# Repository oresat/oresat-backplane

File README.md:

# OreSat Backplane

## Background

The [OreSat](http://oresat.org) CubeSat bus uses a card cage / backplane system based on a 1 Mbps Controller Area Network (CAN) bus and a 2 cell Lithium ion battery power bus (6.0 - 8.4 V). There are ~ 8 cards per CubeSat "U", and the board is meant to be general purpose enough to allow for some card swapping. The RF lines, however, are microstrips on the backplane PCB so the backplane must be rev'd for changes in the RF cards. There are three sets of connectors:

1. 40 pin "Main" connector, which has !shutdown, CAN1, power, CAN2, OreSat power Domain (OPD) lines, and then 5 shared spare pins for custom card interconnects.
2. SMPM RF conncectors, which allows up to 3 RF connector per card and allows for 50 ohm microstrips to be run up and down the the board.
3. 20 pin "Auxiliary" connectors, used on the all but the "end" cards (top and bottom cards), which are for future inter-card communication. Good for Ethernet, for example.

The backplane now comes in two flavors: a 1U backplane, and a 2U backplane.

## Mechanical Specifications

All mechanical specifications for this board are from the SolidWorks model which is in the 'oresat-structure' repo, specifically see the 'Backplane' folder. Some notes on the mechanical design:

- Ring of bare copper on the back is for thermal contact. Assumes annodized Aluminum, so no electrical contact on this ring.
- Backplane is grounded to the Aluminum frame on the internal four fasteners; this requires preparing the Aluminum for an electrical connection.
- Square cutouts on the top and bottom are for the solar connectors to reach the end cards. Note that on the 1U backplane, the bottom cutout is not used.
- Weird cutouts above and below square solar connector cutouts are for shoulder bolts (3 mm Shoulder Diameter, 2 mm Shoulder Length, M2 x 0.4 mm Thread, McMaster Carr #[90263A111](https://www.mcmaster.com/90263a111)) that precisely locates the PCB while allowing some flexing due to differences in thermal expansion between the Aluminum frame and the PCB.
- All other fasteners are M2 x 0.4 x 4 mm.

## Electrical Specifications

The board is designed for a [4 layer stackup](https://docs.oshpark.com/services/four-layer/) from [OSH Park](https://oshpark.com/) which has better RF performance than regular 2 layer board runs.

The connectors that we use on this puppy are the:

- **1.27 mm through-hole vertical socket connectors:**
    - 40 pin main connector
       - Samtec SFM-120-01-S-D-LC
       - 3D CAD: https://www.samtec.com/partnumber/sfm-120-01-s-d-lc
       - Drawing: http://suddendocs.samtec.com/prints/sfm-1xx-xx-xxx-d-xxx-mkt.pdf
       - Brochure: http://suddendocs.samtec.com/catalog_english/sfm.pdf
       - SFM footprint: http://suddendocs.samtec.com/prints/sfm-thd.pdf
    - 20 pin auxiliary connector
       - Samtec SFM-110-01-S-D-LC
       - 3D CAD: https://www.samtec.com/partnumber/sfm-110-01-s-d-lc
       - Drawing: http://suddendocs.samtec.com/prints/sfm-1xx-xx-xxx-d-xxx-mkt.pdf
       - Brochure: http://suddendocs.samtec.com/catalog_english/sfm.pdf
       - SFM footprint: http://suddendocs.samtec.com/prints/sfm-thd.pdf

- **RF (70 cm, L band, S band)**
   - Molex 073300-011X
   - SMPM Connector Plug, Male Pin 50 Ohm Surface Mount, Through Hole Solder, $13.84/ea @ 10
   - Molex (w/CAD): https://www.molex.com/molex/products/datasheet.jsp?part=active/0733000110_RF_COAX_CONNECTORS.xml&channel=Products&Lang=en-US
   - We've done a detailed characteraziation of OSH Park's 4 layer process, and found that 0.38 mm is the correct width for a 50 ohm microstrip.

- **CAN termination**
   - We'll use split termination, using two 60 ohm resistors with a center tapped capacitor for reduced EMI.
   - Resistors
      - 60.4 +/- 1% ohms. Might consider higher if the number of notes (~ 20) adds too much parallel resistance)
      - Usually there's only 2V (differential) across the 120 ohm termination resistors = 16 mA = 33 mW of power dissipation.
      - In the event of a bus short, there's 8.4 V across 120 ohms is 70 mA = 590 mW of power dissipation. That's ~ 300 mW across each of the 60 ohm resistors. Yikes.
      - ISO 11898-2 also requires 220 mW for the termination resistors, for whatever that's worth.
      - There exist 0.5 W 1206 resistors (?!) so although that's for an air rating, we'll still choose it, since larger than 1206 resistors are a tight fit
   - Capacitor
      - ISO 11898-2 doesn't seem to say anything about the capacitance, and the internets tend to say weird things. Unclear on this value.
      - TI's [Controller Area Network Physical Layer Requirements](http://www.ti.com/lit/an/slla270/slla270.pdf) suggests 4.7 nF to make the f_3dB = 1.1 MHz.
      - Seems awfully close to our 1 Mbps bus, so let's bump that down to 1 nF which is f_3db = 5.3 MHz.

- **Debug connector**
   - Harwin M55-6001642R (same family as the solar and end cap connectors)
   - Located on the back side of the backplane, it's a 16 pin 1.27 mm connector that gives external access to CAN busses, VBUS, and the UART lines. It sits in the 1U solar module "cutout".
   - For the external connector board, see the `backplane-debug` folder in the `oresat-flatsat` repo.

## Versions

- 1U
   - v1.0 - First fabbed 1U, but never assembled. For old frames (v1.1 frames), no -Z end cap connector, no debug connector.
   - v1.1 - Added -Z end cap connector. Fabbed roughly 2020-09-01, two assembled.
   - v1.2 - Added 1.27 mm debug connector, which tended to short. Fabbed 2020-12-08. Originally delivered on OreSat0.0 but never flown.
   - v2.0 -new backplane "v2" signal pinout (less power, more signals, UART lines, CAN bus bridging) and new non-shorting debug connector. Made new debug port board and breakout. Also corrected RF ports, including L1 band microstrip and S band strip to -Z end cap. Fabbed 2021-11-01 and installed on OreSat0.1 handed off to Spaceflight, ready for launch!
- 2U
   - v1.0 - First backplane. 2 layer board, RF connector array, aux and main connectors. Fabbed 2018/10/02.
   - v1.1 - End Cards now use 40 pin connector, solar connectors now actually fit. Fabbed 2019/02/25.
   - V2.0 - Switched to 4 layer board, removed RF connector array, used actual microstrips tuned to the 4 layer OSH Park process. Fabbed 2019/07/01.
   - v2.1 - Updated to latest backplane DXF, reducing all sides by 0.15 mm. Fixed solar connector cutout areas that were lopsided. Added CAN termination resistors. Moved RF connectors to latest (2020/02/15) locations. NOT YET FABBED.
   - vHASP - Made for the NASA HASP mission, fabbed, but never used.
   - V2.2 - Updated to FrameV2 and Oresat0.5 card locations

## LICENSE

Copyright the Portland State Aerospace Society, 2022.

This source describes Open Hardware that is licensed under CERN-OHL-S v2, or any later version.

You may redistribute and modify this source and make products using it under the terms of the CERN-OHL-S v2 (https://ohwr.org/cern_ohl_s_v2.txt).

This source is distributed WITHOUT ANY EXPRESS OR IMPLIED WARRANTY, INCLUDING OF MERCHANTABILITY, SATISFACTORY QUALITY AND FITNESS FOR A PARTICULAR PURPOSE. Please see the CERN-OHL-S v2 for applicable conditions.

Source location: https://github.com/oresat/

As per CERN-OHL-S v2 section 4, should You produce hardware based on this source, You must where practicable maintain the Source Location visible on the external case of the Gizmo or other products you make using this source.

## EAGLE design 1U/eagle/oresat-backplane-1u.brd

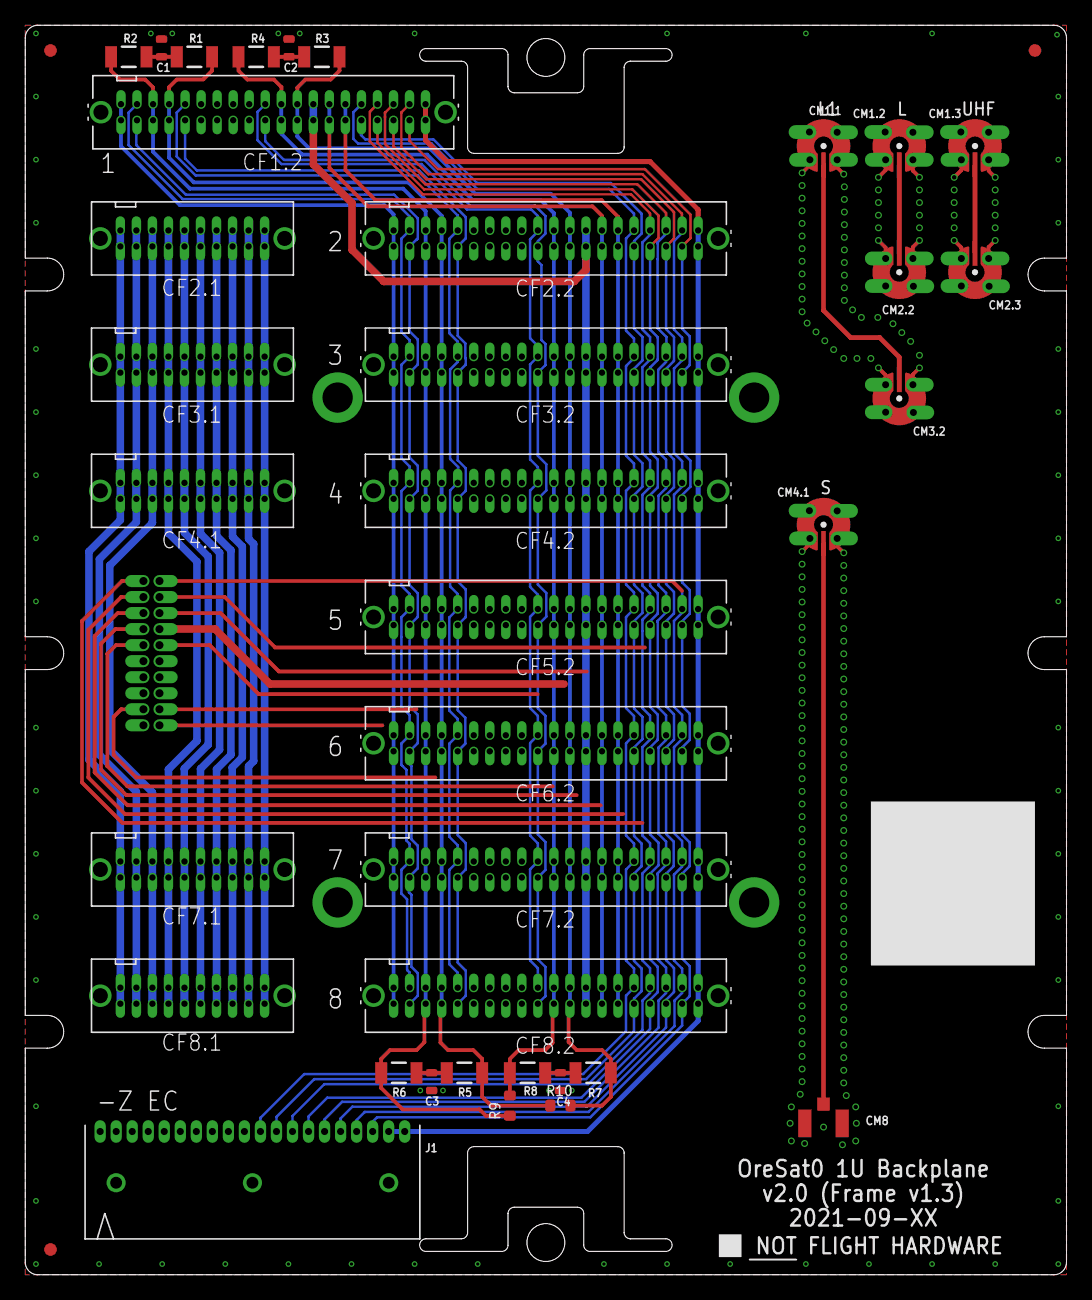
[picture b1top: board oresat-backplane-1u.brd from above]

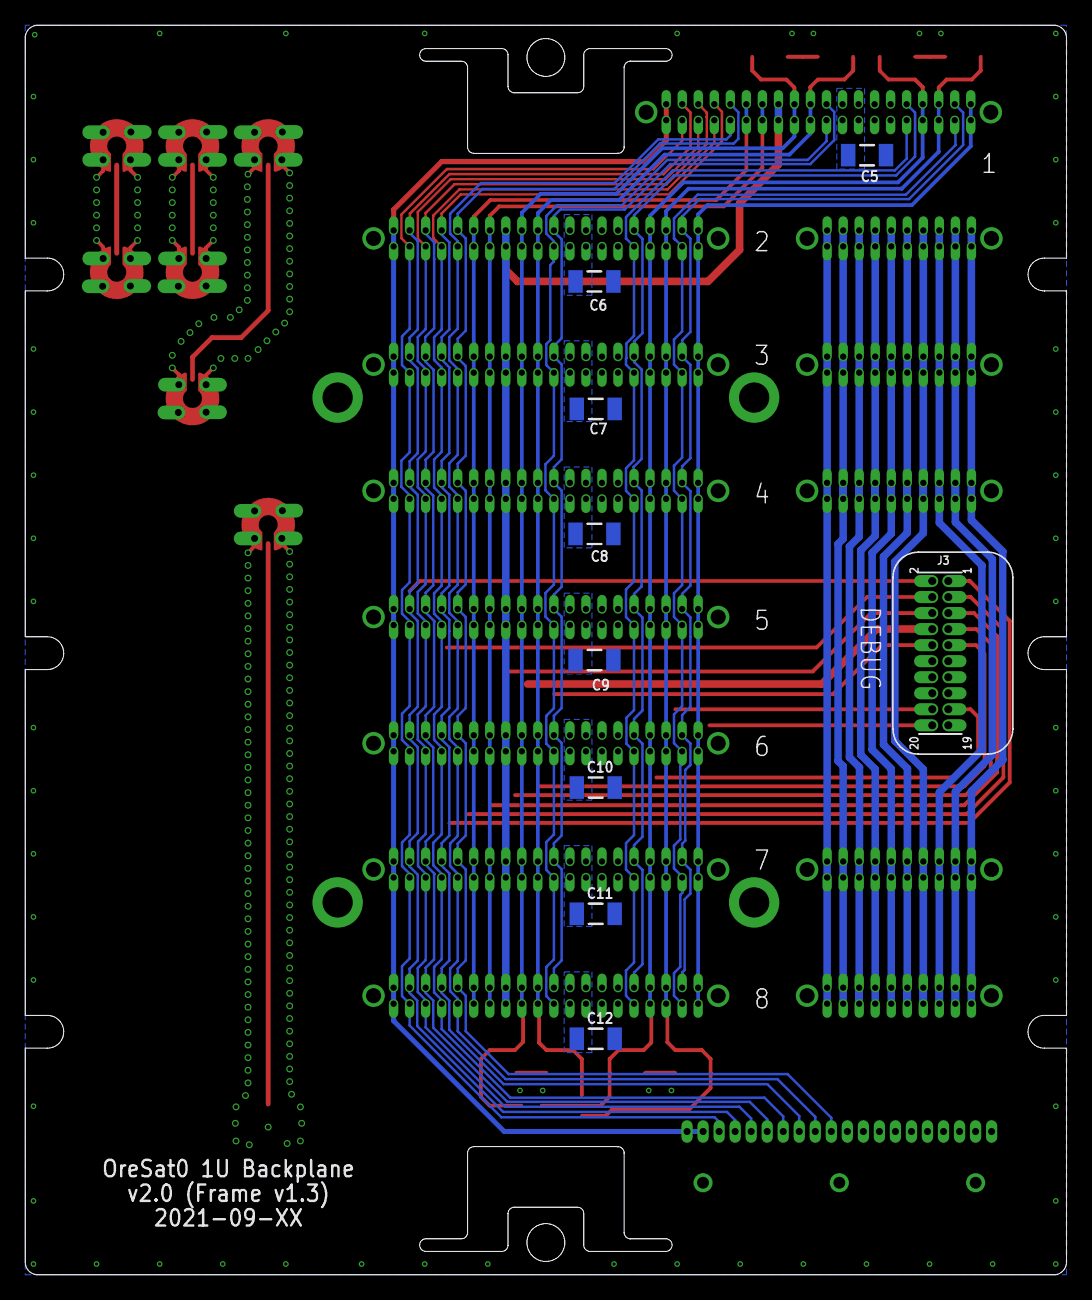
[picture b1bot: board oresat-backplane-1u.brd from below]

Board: 4 copper layers, 82.5 x 99.0 mm, 49 parts (9 on the bottom side), 43 nets.

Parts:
C1, C2, C3, C4: 1n; .0603-C-NOSILK
C5, C6, C7, C8, C9, C10, C11, C12: 1206-B
CF1.2, CF2.2, CF3.2, CF4.2, CF5.2, CF6.2, CF7.2, CF8.2: SFM-120-X1-XXX-D
CF2.1, CF3.1, CF4.1, CF7.1, CF8.1: SFM-110-X1-XXX-D-LC
CM1.1, CM1.2, CM1.3, CM2.2, CM2.3, CM3.2, CM4.1: J-MOLEX-SMPM-73300-0111X
CM8: U.FL-R-SMA; U.FL-R-SMT
FIDUCIAL1, FIDUCIAL2, FIDUCIAL3: FIDUCIAL-1.0X2.0
J1: 5-104196-5
J3: HARWIN-M50-3501042
R1, R2, R3, R4, R5, R6, R7, R8: 60.4; 1206-C
R9, R10: .0603-B-NOSILK
U$1: FLIGHMARKERNEW; FLIGHTMARKER_NEW_BOARDS

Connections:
!SD: CF1.2.39, CF1.2.40, CF2.2.39, CF2.2.40, CF3.2.39, CF3.2.40, CF4.2.39, CF4.2.40, CF5.2.39, CF5.2.40, CF6.2.39, CF6.2.40, CF7.2.39, CF7.2.40, CF8.2.39, CF8.2.40, J3.20
AUX-1: CF2.1.1, CF2.1.2, CF3.1.1, CF3.1.2, CF4.1.1, CF4.1.2, CF7.1.1, CF7.1.2, CF8.1.1, CF8.1.2
AUX-2: CF2.1.3, CF2.1.4, CF3.1.3, CF3.1.4, CF4.1.3, CF4.1.4, CF7.1.3, CF7.1.4, CF8.1.3, CF8.1.4
AUX-3: CF2.1.5, CF2.1.6, CF3.1.5, CF3.1.6, CF4.1.5, CF4.1.6, CF7.1.5, CF7.1.6, CF8.1.5, CF8.1.6
AUX-4: CF2.1.7, CF2.1.8, CF3.1.7, CF3.1.8, CF4.1.7, CF4.1.8, CF7.1.7, CF7.1.8, CF8.1.7, CF8.1.8
AUX-5: CF2.1.9, CF2.1.10, CF3.1.9, CF3.1.10, CF4.1.9, CF4.1.10, CF7.1.9, CF7.1.10, CF8.1.9, CF8.1.10
AUX-6: CF2.1.11, CF2.1.12, CF3.1.11, CF3.1.12, CF4.1.11, CF4.1.12, CF7.1.11, CF7.1.12, CF8.1.11, CF8.1.12
AUX-7: CF2.1.13, CF2.1.14, CF3.1.13, CF3.1.14, CF4.1.13, CF4.1.14, CF7.1.13, CF7.1.14, CF8.1.13, CF8.1.14
AUX-8: CF2.1.15, CF2.1.16, CF3.1.15, CF3.1.16, CF4.1.15, CF4.1.16, CF7.1.15, CF7.1.16, CF8.1.15, CF8.1.16
AUX-9: CF2.1.17, CF2.1.18, CF3.1.17, CF3.1.18, CF4.1.17, CF4.1.18, CF7.1.17, CF7.1.18, CF8.1.17, CF8.1.18
AUX-10: CF2.1.19, CF2.1.20, CF3.1.19, CF3.1.20, CF4.1.19, CF4.1.20, CF7.1.19, CF7.1.20, CF8.1.19, CF8.1.20
CAN1_H: CF1.2.33, CF1.2.34, CF2.2.33, CF2.2.34, CF3.2.33, CF3.2.34, CF4.2.33, CF4.2.34, CF5.2.33, CF5.2.34, CF6.2.33, CF6.2.34, CF7.2.33, CF7.2.34, CF8.2.33, CF8.2.34, J3.17, R1.1, R5.1, R10.1
CAN1_L: CF1.2.35, CF1.2.36, CF2.2.35, CF2.2.36, CF3.2.35, CF3.2.36, CF4.2.35, CF4.2.36, CF5.2.35, CF5.2.36, CF6.2.35, CF6.2.36, CF7.2.35, CF7.2.36, CF8.2.35, CF8.2.36, J3.18, R2.1, R6.1, R9.1
CAN2_H: CF1.2.17, CF1.2.18, CF2.2.17, CF2.2.18, CF3.2.17, CF3.2.18, CF4.2.17, CF4.2.18, CF5.2.17, CF5.2.18, CF6.2.17, CF6.2.18, CF7.2.17, CF7.2.18, CF8.2.17, CF8.2.18, J3.9, R3.1, R7.1, R10.2
CAN2_L: CF1.2.19, CF1.2.20, CF2.2.19, CF2.2.20, CF3.2.19, CF3.2.20, CF4.2.19, CF4.2.20, CF5.2.19, CF5.2.20, CF6.2.19, CF6.2.20, CF7.2.19, CF7.2.20, CF8.2.19, CF8.2.20, J3.10, R4.1, R8.1, R9.2
GND: C1.2, C2.2, C3.2, C4.2, C5.2, C6.2, C7.2, C8.2, C9.2, C10.2, C11.2, C12.2, CF1.2.27, CF1.2.28, CF1.2.29, CF1.2.30, CF1.2.LC1, CF1.2.LC2, CF2.1.LC1, CF2.1.LC2, CF2.2.27, CF2.2.28, CF2.2.29, CF2.2.30, CF2.2.LC1, CF2.2.LC2, CF3.1.LC1, CF3.1.LC2, CF3.2.27, CF3.2.28, CF3.2.29, CF3.2.30, CF3.2.LC1, CF3.2.LC2, CF4.1.LC1, CF4.1.LC2, CF4.2.27, CF4.2.28, CF4.2.29, CF4.2.30, CF4.2.LC1, CF4.2.LC2, CF5.2.27, CF5.2.28, CF5.2.29, CF5.2.30, CF5.2.LC1, CF5.2.LC2, CF6.2.27, CF6.2.28, CF6.2.29, CF6.2.30, CF6.2.LC1, CF6.2.LC2, CF7.1.LC1, CF7.1.LC2, CF7.2.27, CF7.2.28, CF7.2.29, CF7.2.30, CF7.2.LC1, CF7.2.LC2, CF8.1.LC1, CF8.1.LC2, CF8.2.27, CF8.2.28, CF8.2.29, CF8.2.30, CF8.2.LC1, CF8.2.LC2, CM1.1.P$1, CM1.1.P$2, CM1.1.P$3, CM1.1.P$4, CM1.2.P$1, CM1.2.P$2, CM1.2.P$3, CM1.2.P$4, CM1.3.P$1, CM1.3.P$2, CM1.3.P$3, CM1.3.P$4, CM2.2.P$1, CM2.2.P$2, CM2.2.P$3, CM2.2.P$4, CM2.3.P$1, CM2.3.P$2, CM2.3.P$3, CM2.3.P$4, CM3.2.P$1, CM3.2.P$2, CM3.2.P$3, CM3.2.P$4, CM4.1.P$1, CM4.1.P$2, CM4.1.P$3, CM4.1.P$4, CM8.2, CM8.3, J1.HD1, J1.HD2, J1.HD3, J3.14, J3.15, J3.16, J3.19
L1-TURNSTILE: CM1.1.RF-DOWN, CM3.2.RF-DOWN
L-TURNSTILE: CM1.2.RF-DOWN, CM2.2.RF-DOWN
unnamed: C2.1, R3.2, R4.2
unnamed: C1.1, R1.2, R2.2
unnamed: C4.1, R7.2, R8.2
unnamed: C3.1, R5.2, R6.2
OPD_PWR: CF1.2.15, CF1.2.16, CF2.2.15, CF2.2.16, CF3.2.15, CF3.2.16, CF4.2.15, CF4.2.16, CF5.2.15, CF5.2.16, CF6.2.15, CF6.2.16, CF7.2.15, CF7.2.16, CF8.2.15, CF8.2.16, J3.8
OPD_SCL: CF1.2.13, CF1.2.14, CF2.2.13, CF2.2.14, CF3.2.13, CF3.2.14, CF4.2.13, CF4.2.14, CF5.2.13, CF5.2.14, CF6.2.13, CF6.2.14, CF7.2.13, CF7.2.14, CF8.2.13, CF8.2.14, J3.7
OPD_SDA: CF1.2.11, CF1.2.12, CF2.2.11, CF2.2.12, CF3.2.11, CF3.2.12, CF4.2.11, CF4.2.12, CF5.2.11, CF5.2.12, CF6.2.11, CF6.2.12, CF7.2.11, CF7.2.12, CF8.2.11, CF8.2.12, J3.6
S-PATCH: CM4.1.RF-DOWN, CM8.1
SPARE1: CF1.2.1, CF1.2.2, CF2.2.1, CF2.2.2, CF3.2.1, CF3.2.2, CF4.2.1, CF4.2.2, CF5.2.1, CF5.2.2, CF6.2.1, CF6.2.2, CF7.2.1, CF7.2.2, CF8.2.1, CF8.2.2, J1.19, J1.20
SPARE3: CF1.2.3, CF2.2.3, CF3.2.3, CF4.2.3, CF5.2.3, CF6.2.3, CF7.2.3, CF8.2.3, J1.18
SPARE4: CF1.2.4, CF2.2.4, CF3.2.4, CF4.2.4, CF5.2.4, CF6.2.4, CF7.2.4, CF8.2.4, J1.17
SPARE5: CF1.2.5, CF2.2.5, CF3.2.5, CF4.2.5, CF5.2.5, CF6.2.5, CF7.2.5, CF8.2.5, J1.16
SPARE6: CF1.2.6, CF2.2.6, CF3.2.6, CF4.2.6, CF5.2.6, CF6.2.6, CF7.2.6, CF8.2.6, J1.15
SPARE7: CF1.2.7, CF2.2.7, CF3.2.7, CF4.2.7, CF5.2.7, CF6.2.7, CF7.2.7, CF8.2.7, J1.14
SPARE8: CF1.2.8, CF2.2.8, CF3.2.8, CF4.2.8, CF5.2.8, CF6.2.8, CF7.2.8, CF8.2.8, J1.13
SPARE9: CF1.2.9, CF2.2.9, CF3.2.9, CF4.2.9, CF5.2.9, CF6.2.9, CF7.2.9, CF8.2.9, J1.12
SPARE10: CF1.2.10, CF2.2.10, CF3.2.10, CF4.2.10, CF5.2.10, CF6.2.10, CF7.2.10, CF8.2.10, J1.11
SPARE21: CF1.2.21, CF2.2.21, CF3.2.21, CF4.2.21, CF5.2.21, CF6.2.21, CF7.2.21, CF8.2.21
SPARE22: CF1.2.22, CF2.2.22, CF3.2.22, CF4.2.22, CF5.2.22, CF6.2.22, CF7.2.22, CF8.2.22
SPARE31: CF1.2.31, CF2.2.31, CF3.2.31, CF4.2.31, CF5.2.31, CF6.2.31, CF7.2.31, CF8.2.31
SPARE32: CF1.2.32, CF2.2.32, CF3.2.32, CF4.2.32, CF5.2.32, CF6.2.32, CF7.2.32, CF8.2.32
UART-RX: CF1.2.38, CF2.2.38, CF3.2.38, CF4.2.38, CF5.2.38, CF6.2.38, CF7.2.38, CF8.2.38
UART-TX: CF1.2.37, CF2.2.37, CF3.2.37, CF4.2.37, CF5.2.37, CF6.2.37, CF7.2.37, CF8.2.37
UHF-TURNSTILE: CM1.3.RF-DOWN, CM2.3.RF-DOWN
VBUS: C5.1, C6.1, C7.1, C8.1, C9.1, C10.1, C11.1, C12.1, CF1.2.23, CF1.2.24, CF1.2.25, CF1.2.26, CF2.2.23, CF2.2.24, CF2.2.25, CF2.2.26, CF3.2.23, CF3.2.24, CF3.2.25, CF3.2.26, CF4.2.23, CF4.2.24, CF4.2.25, CF4.2.26, CF5.2.23, CF5.2.24, CF5.2.25, CF5.2.26, CF6.2.23, CF6.2.24, CF6.2.25, CF6.2.26, CF7.2.23, CF7.2.24, CF7.2.25, CF7.2.26, CF8.2.23, CF8.2.24, CF8.2.25, CF8.2.26, J3.11, J3.12, J3.13

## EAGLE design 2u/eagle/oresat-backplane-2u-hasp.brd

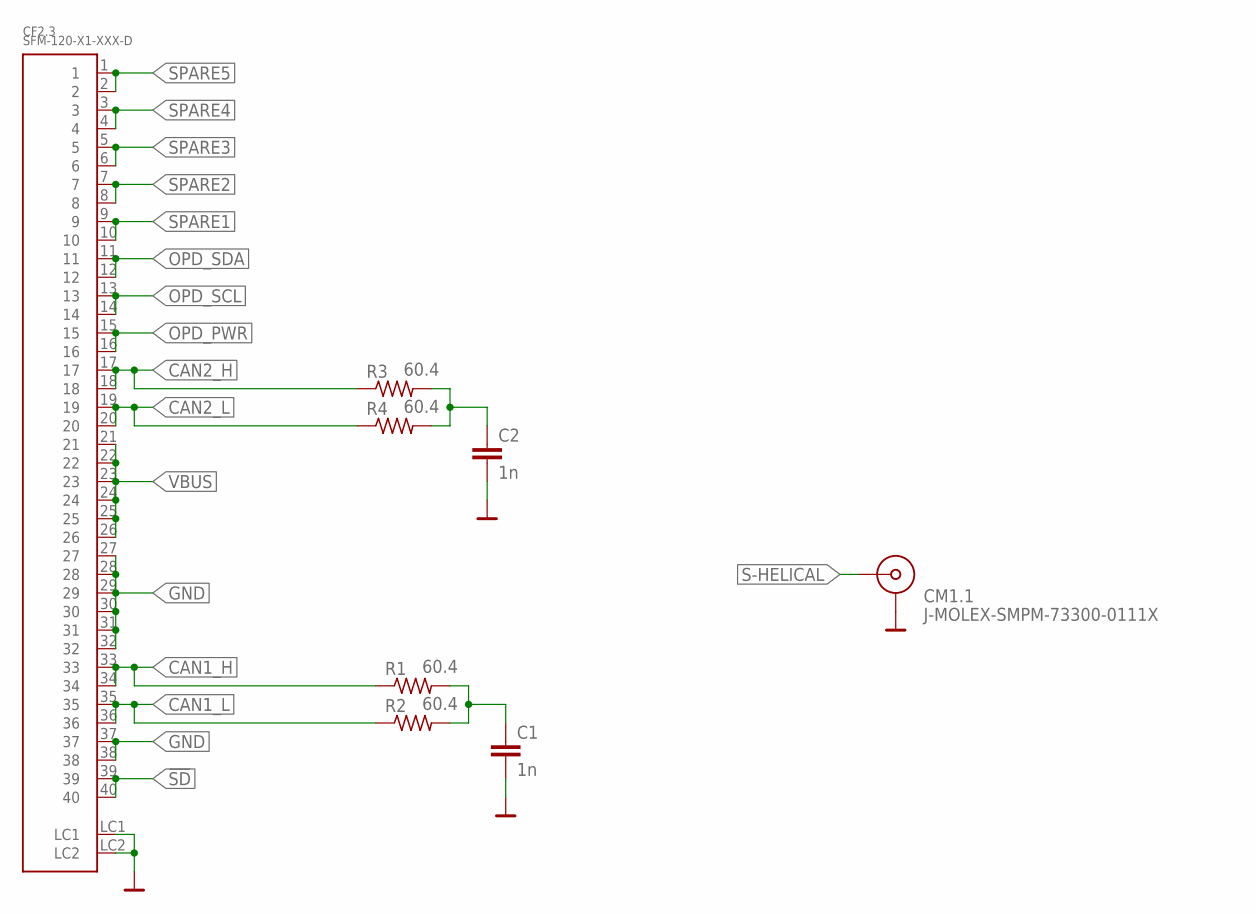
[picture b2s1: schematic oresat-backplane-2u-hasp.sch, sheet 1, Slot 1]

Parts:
C1, C2: 1n; .0603-C-NOSILK
CF2.3: SFM-120-X1-XXX-D
CM1.1: J-MOLEX-SMPM-73300-0111X
R1, R2, R3, R4: 60.4; 1206-C

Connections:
!SD: CF2.3.39, CF2.3.40; also elsewhere on the board
CAN1_H: CF2.3.33, CF2.3.34, R1.1; also elsewhere on the board
CAN1_L: CF2.3.35, CF2.3.36, R2.1; also elsewhere on the board
CAN2_H: CF2.3.17, CF2.3.18, R3.1; also elsewhere on the board
CAN2_L: CF2.3.19, CF2.3.20, R4.1; also elsewhere on the board
GND: C1.2, C2.2, CF2.3.27, CF2.3.28, CF2.3.29, CF2.3.30, CF2.3.31, CF2.3.32, CF2.3.37, CF2.3.38, CF2.3.LC1, CF2.3.LC2, CM1.1.P$1 (SHIELD1), CM1.1.P$2 (SHIELD1), CM1.1.P$3 (SHIELD1), CM1.1.P$4 (SHIELD1); also elsewhere on the board
unnamed: C2.1, R3.2, R4.2
unnamed: C1.1, R1.2, R2.2
OPD_PWR: CF2.3.15, CF2.3.16; also elsewhere on the board
OPD_SCL: CF2.3.13, CF2.3.14; also elsewhere on the board
OPD_SDA: CF2.3.11, CF2.3.12; also elsewhere on the board
S-HELICAL: CM1.1.RF-DOWN (RF); also elsewhere on the board
SPARE1: CF2.3.9, CF2.3.10; also elsewhere on the board
SPARE2: CF2.3.7, CF2.3.8; also elsewhere on the board
SPARE3: CF2.3.5, CF2.3.6; also elsewhere on the board
SPARE4: CF2.3.3, CF2.3.4; also elsewhere on the board
SPARE5: CF2.3.1, CF2.3.2; also elsewhere on the board
VBUS: CF2.3.21, CF2.3.22, CF2.3.23, CF2.3.24, CF2.3.25, CF2.3.26; also elsewhere on the board

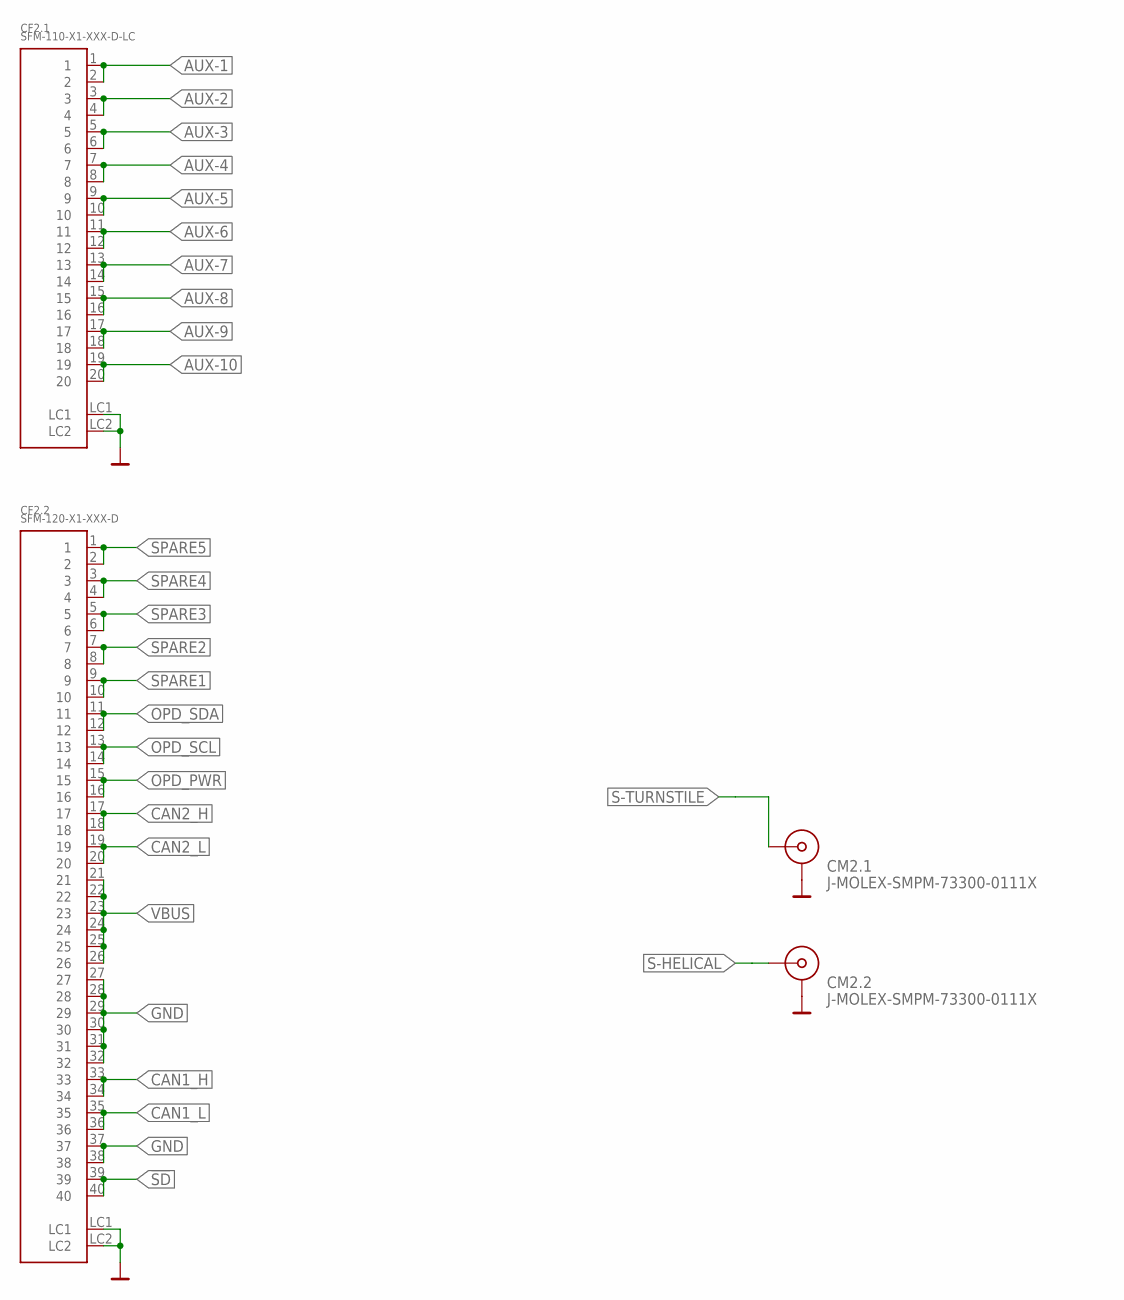
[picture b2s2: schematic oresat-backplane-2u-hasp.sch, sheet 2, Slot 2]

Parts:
CF2.1: SFM-110-X1-XXX-D-LC
CF2.2: SFM-120-X1-XXX-D
CM2.1, CM2.2: J-MOLEX-SMPM-73300-0111X

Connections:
!SD: CF2.2.39, CF2.2.40; also elsewhere on the board
AUX-1: CF2.1.1, CF2.1.2; also elsewhere on the board
AUX-2: CF2.1.3, CF2.1.4; also elsewhere on the board
AUX-3: CF2.1.5, CF2.1.6; also elsewhere on the board
AUX-4: CF2.1.7, CF2.1.8; also elsewhere on the board
AUX-5: CF2.1.9, CF2.1.10; also elsewhere on the board
AUX-6: CF2.1.11, CF2.1.12; also elsewhere on the board
AUX-7: CF2.1.13, CF2.1.14; also elsewhere on the board
AUX-8: CF2.1.15, CF2.1.16; also elsewhere on the board
AUX-9: CF2.1.17, CF2.1.18; also elsewhere on the board
AUX-10: CF2.1.19, CF2.1.20; also elsewhere on the board
CAN1_H: CF2.2.33, CF2.2.34; also elsewhere on the board
CAN1_L: CF2.2.35, CF2.2.36; also elsewhere on the board
CAN2_H: CF2.2.17, CF2.2.18; also elsewhere on the board
CAN2_L: CF2.2.19, CF2.2.20; also elsewhere on the board
GND: CF2.1.LC1, CF2.1.LC2, CF2.2.27, CF2.2.28, CF2.2.29, CF2.2.30, CF2.2.31, CF2.2.32, CF2.2.37, CF2.2.38, CF2.2.LC1, CF2.2.LC2, CM2.1.P$1 (SHIELD1), CM2.1.P$2 (SHIELD1), CM2.1.P$3 (SHIELD1), CM2.1.P$4 (SHIELD1), CM2.2.P$1 (SHIELD1), CM2.2.P$2 (SHIELD1), CM2.2.P$3 (SHIELD1), CM2.2.P$4 (SHIELD1); also elsewhere on the board
OPD_PWR: CF2.2.15, CF2.2.16; also elsewhere on the board
OPD_SCL: CF2.2.13, CF2.2.14; also elsewhere on the board
OPD_SDA: CF2.2.11, CF2.2.12; also elsewhere on the board
S-HELICAL: CM2.2.RF-DOWN (RF); also elsewhere on the board
S-TURNSTILE: CM2.1.RF-DOWN (RF); also elsewhere on the board
SPARE1: CF2.2.9, CF2.2.10; also elsewhere on the board
SPARE2: CF2.2.7, CF2.2.8; also elsewhere on the board
SPARE3: CF2.2.5, CF2.2.6; also elsewhere on the board
SPARE4: CF2.2.3, CF2.2.4; also elsewhere on the board
SPARE5: CF2.2.1, CF2.2.2; also elsewhere on the board
VBUS: CF2.2.21, CF2.2.22, CF2.2.23, CF2.2.24, CF2.2.25, CF2.2.26; also elsewhere on the board

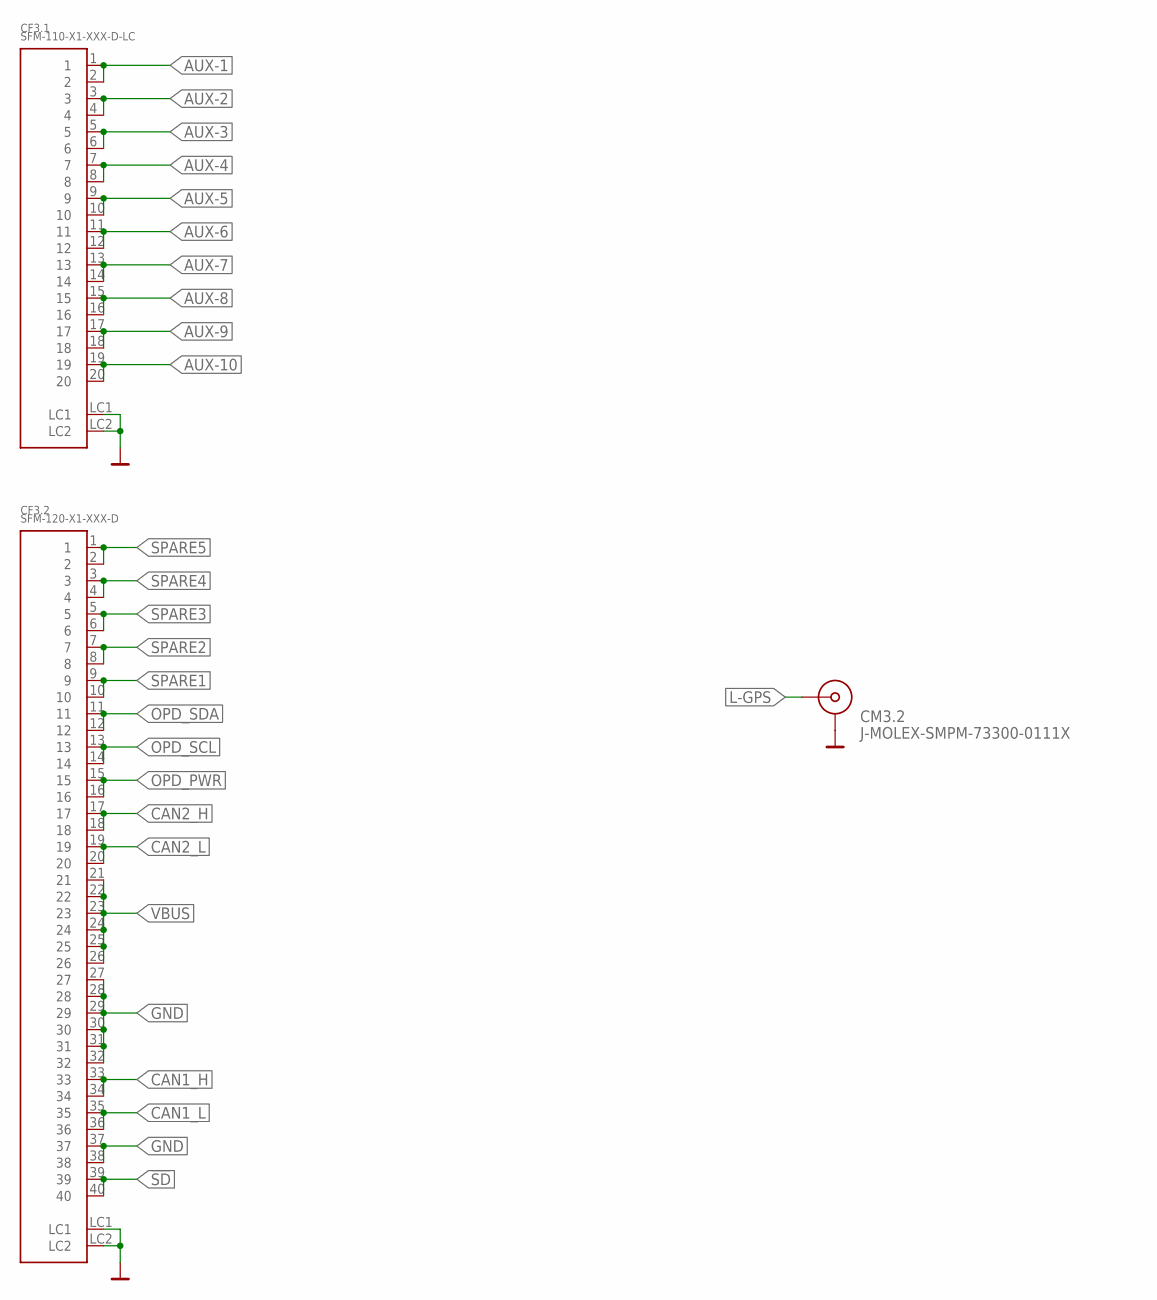
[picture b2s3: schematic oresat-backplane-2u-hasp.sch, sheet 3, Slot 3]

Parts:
CF3.1: SFM-110-X1-XXX-D-LC
CF3.2: SFM-120-X1-XXX-D
CM3.2: J-MOLEX-SMPM-73300-0111X

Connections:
!SD: CF3.2.39, CF3.2.40; also elsewhere on the board
AUX-1: CF3.1.1, CF3.1.2; also elsewhere on the board
AUX-2: CF3.1.3, CF3.1.4; also elsewhere on the board
AUX-3: CF3.1.5, CF3.1.6; also elsewhere on the board
AUX-4: CF3.1.7, CF3.1.8; also elsewhere on the board
AUX-5: CF3.1.9, CF3.1.10; also elsewhere on the board
AUX-6: CF3.1.11, CF3.1.12; also elsewhere on the board
AUX-7: CF3.1.13, CF3.1.14; also elsewhere on the board
AUX-8: CF3.1.15, CF3.1.16; also elsewhere on the board
AUX-9: CF3.1.17, CF3.1.18; also elsewhere on the board
AUX-10: CF3.1.19, CF3.1.20; also elsewhere on the board
CAN1_H: CF3.2.33, CF3.2.34; also elsewhere on the board
CAN1_L: CF3.2.35, CF3.2.36; also elsewhere on the board
CAN2_H: CF3.2.17, CF3.2.18; also elsewhere on the board
CAN2_L: CF3.2.19, CF3.2.20; also elsewhere on the board
GND: CF3.1.LC1, CF3.1.LC2, CF3.2.27, CF3.2.28, CF3.2.29, CF3.2.30, CF3.2.31, CF3.2.32, CF3.2.37, CF3.2.38, CF3.2.LC1, CF3.2.LC2, CM3.2.P$1 (SHIELD1), CM3.2.P$2 (SHIELD1), CM3.2.P$3 (SHIELD1), CM3.2.P$4 (SHIELD1); also elsewhere on the board
L-GPS: CM3.2.RF-DOWN (RF); also elsewhere on the board
OPD_PWR: CF3.2.15, CF3.2.16; also elsewhere on the board
OPD_SCL: CF3.2.13, CF3.2.14; also elsewhere on the board
OPD_SDA: CF3.2.11, CF3.2.12; also elsewhere on the board
SPARE1: CF3.2.9, CF3.2.10; also elsewhere on the board
SPARE2: CF3.2.7, CF3.2.8; also elsewhere on the board
SPARE3: CF3.2.5, CF3.2.6; also elsewhere on the board
SPARE4: CF3.2.3, CF3.2.4; also elsewhere on the board
SPARE5: CF3.2.1, CF3.2.2; also elsewhere on the board
VBUS: CF3.2.21, CF3.2.22, CF3.2.23, CF3.2.24, CF3.2.25, CF3.2.26; also elsewhere on the board

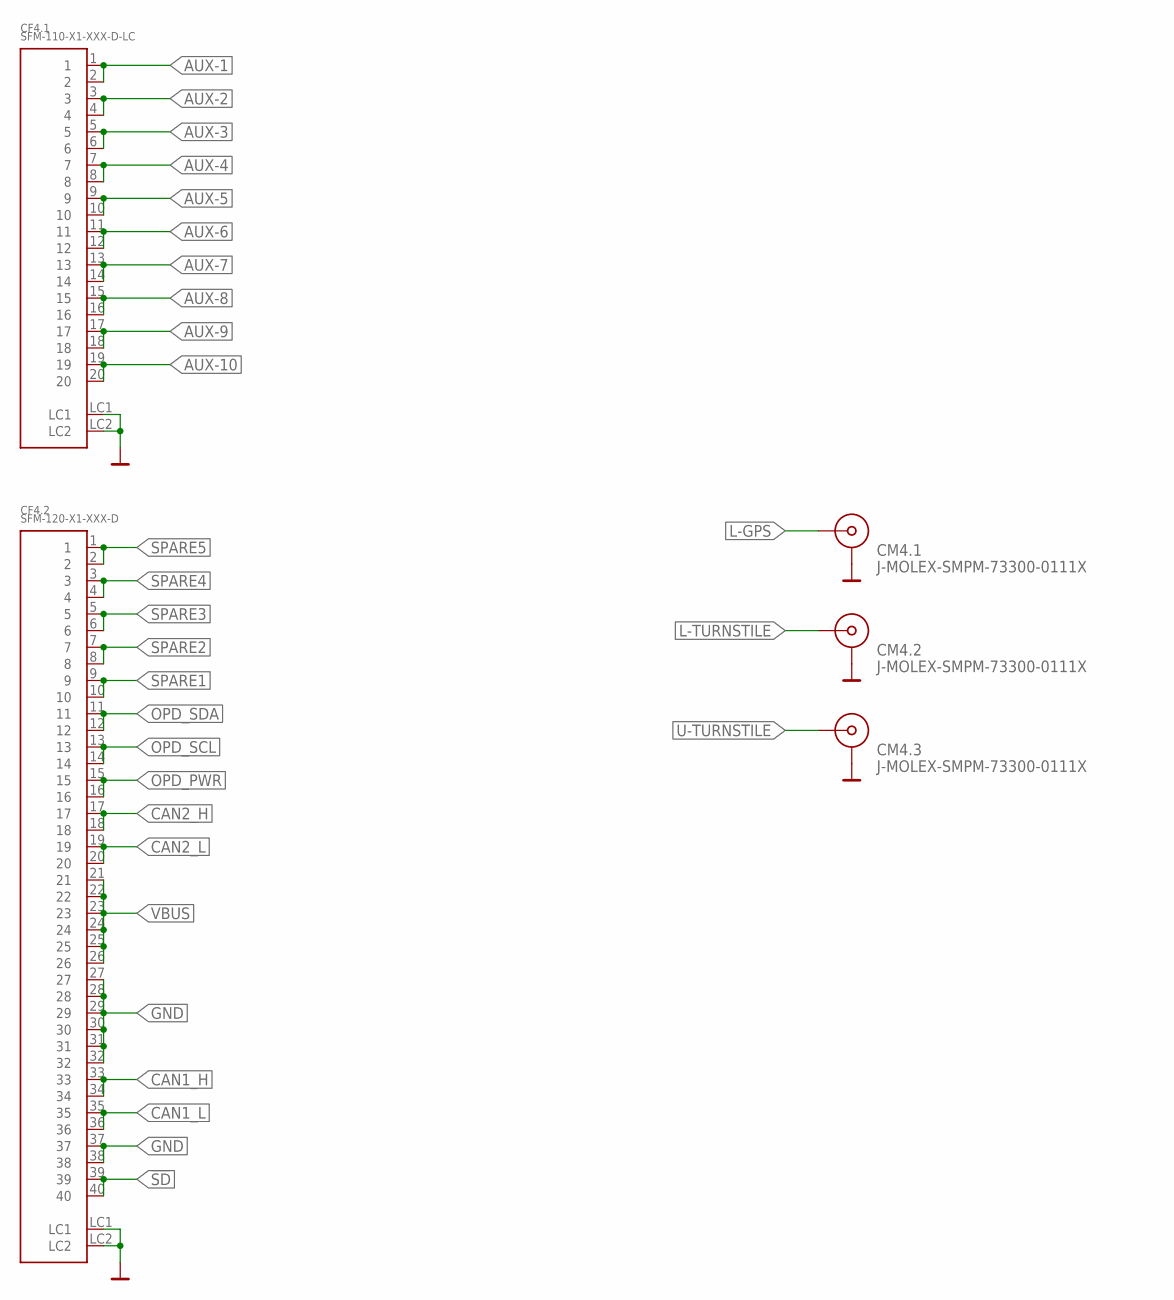
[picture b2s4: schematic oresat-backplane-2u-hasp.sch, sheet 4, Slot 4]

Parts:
CF4.1: SFM-110-X1-XXX-D-LC
CF4.2: SFM-120-X1-XXX-D
CM4.1, CM4.2, CM4.3: J-MOLEX-SMPM-73300-0111X

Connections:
!SD: CF4.2.39, CF4.2.40; also elsewhere on the board
AUX-1: CF4.1.1, CF4.1.2; also elsewhere on the board
AUX-2: CF4.1.3, CF4.1.4; also elsewhere on the board
AUX-3: CF4.1.5, CF4.1.6; also elsewhere on the board
AUX-4: CF4.1.7, CF4.1.8; also elsewhere on the board
AUX-5: CF4.1.9, CF4.1.10; also elsewhere on the board
AUX-6: CF4.1.11, CF4.1.12; also elsewhere on the board
AUX-7: CF4.1.13, CF4.1.14; also elsewhere on the board
AUX-8: CF4.1.15, CF4.1.16; also elsewhere on the board
AUX-9: CF4.1.17, CF4.1.18; also elsewhere on the board
AUX-10: CF4.1.19, CF4.1.20; also elsewhere on the board
CAN1_H: CF4.2.33, CF4.2.34; also elsewhere on the board
CAN1_L: CF4.2.35, CF4.2.36; also elsewhere on the board
CAN2_H: CF4.2.17, CF4.2.18; also elsewhere on the board
CAN2_L: CF4.2.19, CF4.2.20; also elsewhere on the board
GND: CF4.1.LC1, CF4.1.LC2, CF4.2.27, CF4.2.28, CF4.2.29, CF4.2.30, CF4.2.31, CF4.2.32, CF4.2.37, CF4.2.38, CF4.2.LC1, CF4.2.LC2, CM4.1.P$1 (SHIELD1), CM4.1.P$2 (SHIELD1), CM4.1.P$3 (SHIELD1), CM4.1.P$4 (SHIELD1), CM4.2.P$1 (SHIELD1), CM4.2.P$2 (SHIELD1), CM4.2.P$3 (SHIELD1), CM4.2.P$4 (SHIELD1), CM4.3.P$1 (SHIELD1), CM4.3.P$2 (SHIELD1), CM4.3.P$3 (SHIELD1), CM4.3.P$4 (SHIELD1); also elsewhere on the board
L-GPS: CM4.1.RF-DOWN (RF); also elsewhere on the board
L-TURNSTILE: CM4.2.RF-DOWN (RF); also elsewhere on the board
OPD_PWR: CF4.2.15, CF4.2.16; also elsewhere on the board
OPD_SCL: CF4.2.13, CF4.2.14; also elsewhere on the board
OPD_SDA: CF4.2.11, CF4.2.12; also elsewhere on the board
SPARE1: CF4.2.9, CF4.2.10; also elsewhere on the board
SPARE2: CF4.2.7, CF4.2.8; also elsewhere on the board
SPARE3: CF4.2.5, CF4.2.6; also elsewhere on the board
SPARE4: CF4.2.3, CF4.2.4; also elsewhere on the board
SPARE5: CF4.2.1, CF4.2.2; also elsewhere on the board
U-TURNSTILE: CM4.3.RF-DOWN (RF); also elsewhere on the board
VBUS: CF4.2.21, CF4.2.22, CF4.2.23, CF4.2.24, CF4.2.25, CF4.2.26; also elsewhere on the board

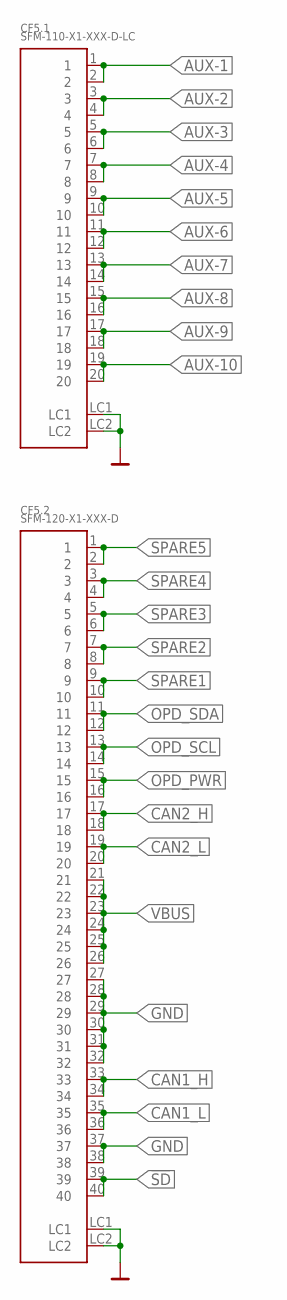
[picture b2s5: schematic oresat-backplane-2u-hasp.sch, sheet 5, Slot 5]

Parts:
CF5.1: SFM-110-X1-XXX-D-LC
CF5.2: SFM-120-X1-XXX-D

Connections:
!SD: CF5.2.39, CF5.2.40; also elsewhere on the board
AUX-1: CF5.1.1, CF5.1.2; also elsewhere on the board
AUX-2: CF5.1.3, CF5.1.4; also elsewhere on the board
AUX-3: CF5.1.5, CF5.1.6; also elsewhere on the board
AUX-4: CF5.1.7, CF5.1.8; also elsewhere on the board
AUX-5: CF5.1.9, CF5.1.10; also elsewhere on the board
AUX-6: CF5.1.11, CF5.1.12; also elsewhere on the board
AUX-7: CF5.1.13, CF5.1.14; also elsewhere on the board
AUX-8: CF5.1.15, CF5.1.16; also elsewhere on the board
AUX-9: CF5.1.17, CF5.1.18; also elsewhere on the board
AUX-10: CF5.1.19, CF5.1.20; also elsewhere on the board
CAN1_H: CF5.2.33, CF5.2.34; also elsewhere on the board
CAN1_L: CF5.2.35, CF5.2.36; also elsewhere on the board
CAN2_H: CF5.2.17, CF5.2.18; also elsewhere on the board
CAN2_L: CF5.2.19, CF5.2.20; also elsewhere on the board
GND: CF5.1.LC1, CF5.1.LC2, CF5.2.27, CF5.2.28, CF5.2.29, CF5.2.30, CF5.2.31, CF5.2.32, CF5.2.37, CF5.2.38, CF5.2.LC1, CF5.2.LC2; also elsewhere on the board
OPD_PWR: CF5.2.15, CF5.2.16; also elsewhere on the board
OPD_SCL: CF5.2.13, CF5.2.14; also elsewhere on the board
OPD_SDA: CF5.2.11, CF5.2.12; also elsewhere on the board
SPARE1: CF5.2.9, CF5.2.10; also elsewhere on the board
SPARE2: CF5.2.7, CF5.2.8; also elsewhere on the board
SPARE3: CF5.2.5, CF5.2.6; also elsewhere on the board
SPARE4: CF5.2.3, CF5.2.4; also elsewhere on the board
SPARE5: CF5.2.1, CF5.2.2; also elsewhere on the board
VBUS: CF5.2.21, CF5.2.22, CF5.2.23, CF5.2.24, CF5.2.25, CF5.2.26; also elsewhere on the board

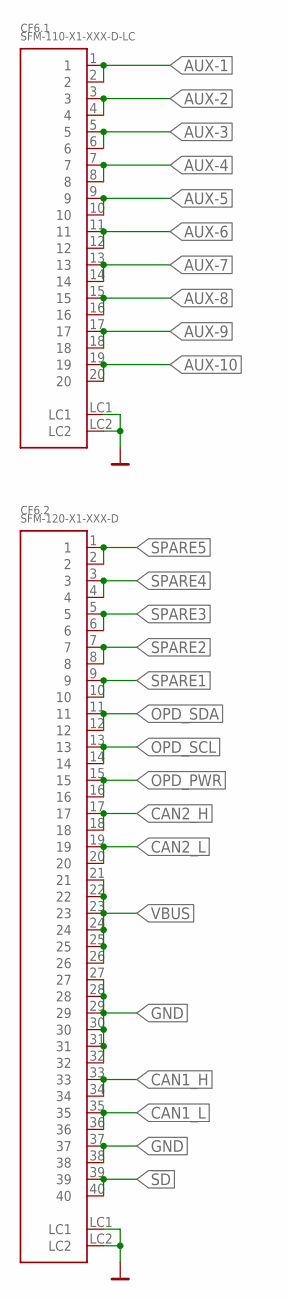
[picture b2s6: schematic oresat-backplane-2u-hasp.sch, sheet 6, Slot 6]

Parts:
CF6.1: SFM-110-X1-XXX-D-LC
CF6.2: SFM-120-X1-XXX-D

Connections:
!SD: CF6.2.39, CF6.2.40; also elsewhere on the board
AUX-1: CF6.1.1, CF6.1.2; also elsewhere on the board
AUX-2: CF6.1.3, CF6.1.4; also elsewhere on the board
AUX-3: CF6.1.5, CF6.1.6; also elsewhere on the board
AUX-4: CF6.1.7, CF6.1.8; also elsewhere on the board
AUX-5: CF6.1.9, CF6.1.10; also elsewhere on the board
AUX-6: CF6.1.11, CF6.1.12; also elsewhere on the board
AUX-7: CF6.1.13, CF6.1.14; also elsewhere on the board
AUX-8: CF6.1.15, CF6.1.16; also elsewhere on the board
AUX-9: CF6.1.17, CF6.1.18; also elsewhere on the board
AUX-10: CF6.1.19, CF6.1.20; also elsewhere on the board
CAN1_H: CF6.2.33, CF6.2.34; also elsewhere on the board
CAN1_L: CF6.2.35, CF6.2.36; also elsewhere on the board
CAN2_H: CF6.2.17, CF6.2.18; also elsewhere on the board
CAN2_L: CF6.2.19, CF6.2.20; also elsewhere on the board
GND: CF6.1.LC1, CF6.1.LC2, CF6.2.27, CF6.2.28, CF6.2.29, CF6.2.30, CF6.2.31, CF6.2.32, CF6.2.37, CF6.2.38, CF6.2.LC1, CF6.2.LC2; also elsewhere on the board
OPD_PWR: CF6.2.15, CF6.2.16; also elsewhere on the board
OPD_SCL: CF6.2.13, CF6.2.14; also elsewhere on the board
OPD_SDA: CF6.2.11, CF6.2.12; also elsewhere on the board
SPARE1: CF6.2.9, CF6.2.10; also elsewhere on the board
SPARE2: CF6.2.7, CF6.2.8; also elsewhere on the board
SPARE3: CF6.2.5, CF6.2.6; also elsewhere on the board
SPARE4: CF6.2.3, CF6.2.4; also elsewhere on the board
SPARE5: CF6.2.1, CF6.2.2; also elsewhere on the board
VBUS: CF6.2.21, CF6.2.22, CF6.2.23, CF6.2.24, CF6.2.25, CF6.2.26; also elsewhere on the board

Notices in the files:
parts and their libraries:
COPYRIGHT: Copyright (C) 2021 Ultra Librarian. All rights reserved.
